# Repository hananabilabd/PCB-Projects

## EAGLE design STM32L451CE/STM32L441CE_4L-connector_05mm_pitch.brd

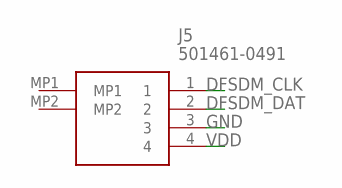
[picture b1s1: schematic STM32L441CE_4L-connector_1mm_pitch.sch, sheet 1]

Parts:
J5: 501461-0491; 5014610491

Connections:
DFSDM_CLK: J5.1; also elsewhere on the board
DFSDM_DAT: J5.2; also elsewhere on the board
GND: J5.3; also elsewhere on the board
VDD: J5.4; also elsewhere on the board

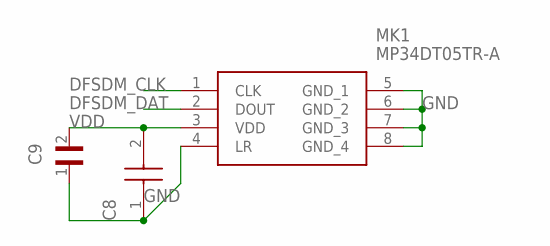
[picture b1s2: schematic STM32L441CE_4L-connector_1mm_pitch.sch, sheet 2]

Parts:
C8: AMK063AC6105KP-F; CAPC0603X33N
C9: GRM033C80J104KE15D; CAPC0603X33N
MK1: MP34DT05TR-A; MP34DT05TRA

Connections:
DFSDM_CLK: MK1.1 (CLK); also elsewhere on the board
DFSDM_DAT: MK1.2 (DOUT); also elsewhere on the board
GND: C8.1, C9.1, MK1.4 (LR), MK1.5 (GND_1), MK1.6 (GND_2), MK1.7 (GND_3), MK1.8 (GND_4); also elsewhere on the board
VDD: C8.2, C9.2, MK1.3 (VDD); also elsewhere on the board

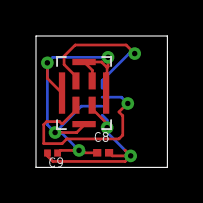
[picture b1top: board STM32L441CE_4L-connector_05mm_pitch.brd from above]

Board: 4 copper layers, 7.3 x 7.3 mm, 4 parts (1 on the bottom side), 4 nets.

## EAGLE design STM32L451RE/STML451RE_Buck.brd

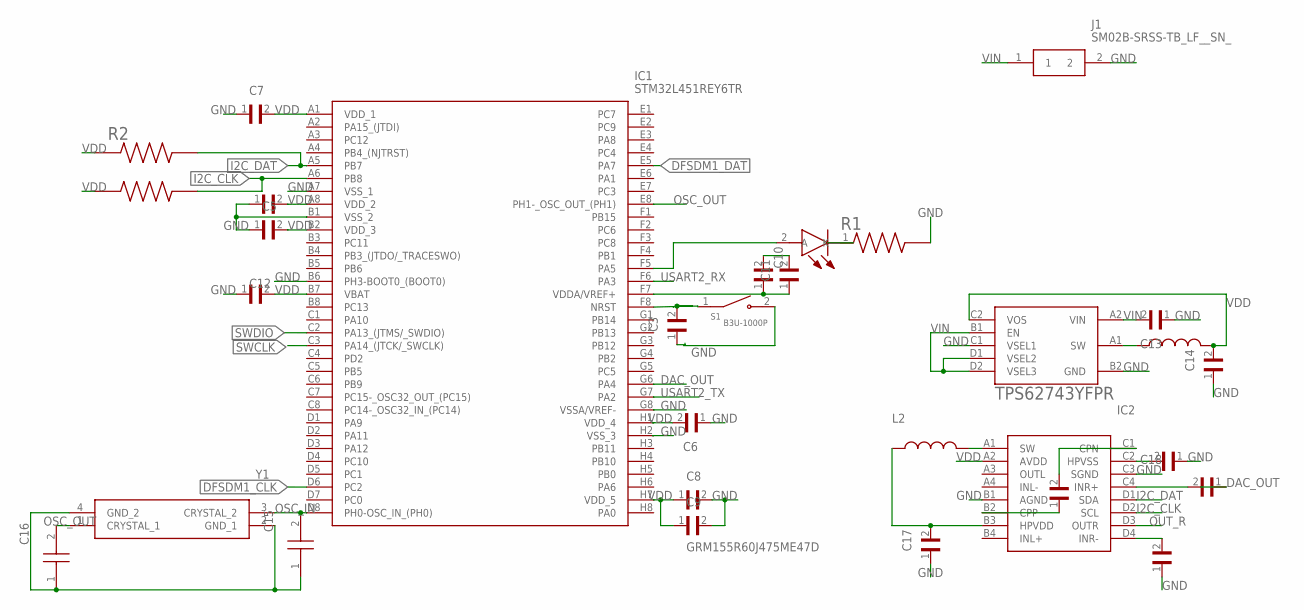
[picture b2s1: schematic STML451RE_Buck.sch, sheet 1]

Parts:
C3, C4, C5, C6, C7, C8, C10, C12: GRM033C80J104KE15D; CAPC0603X33N
C9, C13: GRM155R60J475ME47D; CAPC1005X60N
C11, C19, C20, C21: JMK105C6105KV-F; CAPC1005X55N
C14: GRM155R60J106ME15D; CAPC1005X65N
C15, C16: 0101YA120JAT2A; CAPC0402X22N
C17, C18: GRM155R60J225KE95D; CAPC1005X55N
IC1: STM32L451REY6TR; BGA64C40P8X8_336X366X58
IC2: TPA6140A2YFFT; BGA16C40P4X4_156X156X63
J1: SM02B-SRSS-TB_LF__SN_; SM02B-SRSS-TB
L1: 1285AS-H-2R2M=P2; INDC2016X100N
L2: LQM21PN2R2MC0D; INDC2012X55N
LED1: VLMS1500-GS08; VLMG1500GS08
R1: CRCW02012K20FKED; RESC0603X28N
R2, R3: ERA-2AEB122X; RESC1005X40N
S1: B3U-1000P; SW_B3U-1000P
U1: TPS62743YFPR; BGA8N40P2X4_87X156X50
Y1: FL0800008Q

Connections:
DAC_OUT: C21.1, IC1.G6 (PA4)
DFSDM1_CLK: IC1.D6 (PC2); also elsewhere on the board
DFSDM1_DAT: IC1.E5 (PA7); also elsewhere on the board
GND: C3.1, C4.1, C5.1, C6.1, C7.1, C8.2, C9.2, C12.1, C13.1, C14.1, C15.1, C16.1, C17.1, C18.1, C20.1, IC1.A7 (VSS_1), IC1.B1 (VSS_2), IC1.B6 (PH3-BOOT0_(BOOT0)), IC1.G8 (VSSA/VREF-), IC1.H2 (VSS_3), IC2.B1 (AGND), IC2.C3 (SGND), J1.2, R1.2, U1.B2 (GND), U1.C1 (VSEL1), Y1.2 (GND_1), Y1.4 (GND_2); also elsewhere on the board
I2C_CLK: IC1.A6 (PB8), IC2.D2 (SCL), R3.2
I2C_DAT: IC1.A5 (PB7), IC2.D1 (SDA), R2.2
unnamed: IC1.F5 (PA5), LED1.2 (A)
unnamed: C3.2, S1.1
unnamed: C10.1, C11.1, IC1.F7 (VDDA/VREF+)
unnamed: C10.2, C11.2
unnamed: LED1.1 (K), R1.1
unnamed: C17.2, IC2.B3 (HPVDD), L2.1
unnamed: L1.1, U1.A1 (SW)
unnamed: IC2.A1 (SW), L2.2
unnamed: C18.2, IC2.C2 (HPVSS)
unnamed: C19.1, IC2.B2 (CPP)
unnamed: C19.2, IC2.C1 (CPN)
unnamed: C21.2, IC2.C4 (INR+)
unnamed: C20.2, IC2.D4 (INR-)
OSC_IN: C15.2, IC1.D8 (PH0-OSC_IN_(PH0)), Y1.3 (CRYSTAL_2)
OSC_OUT: C16.2, IC1.E8 (PH1-_OSC_OUT_(PH1)), Y1.1 (CRYSTAL_1)
OUT_R: IC2.D3 (OUTR)
SWCLK: IC1.C3 (PA14_(JTCK/_SWCLK))
SWDIO: IC1.C2 (PA13_(JTMS/_SWDIO))
USART2_RX: IC1.F6 (PA3)
USART2_TX: IC1.G7 (PA2)
VDD: C4.2, C5.2, C6.2, C7.2, C8.1, C9.1, C12.2, C14.2, IC1.A1 (VDD_1), IC1.A8 (VDD_2), IC1.B2 (VDD_3), IC1.B7 (VBAT), IC1.H1 (VDD_4), IC1.H7 (VDD_5), IC2.A2 (AVDD), L1.2, R2.1, R3.1, U1.C2 (VOS); also elsewhere on the board
VIN: C13.2, J1.1, U1.A2 (VIN), U1.B1 (EN), U1.D1 (VSEL2), U1.D2 (VSEL3)

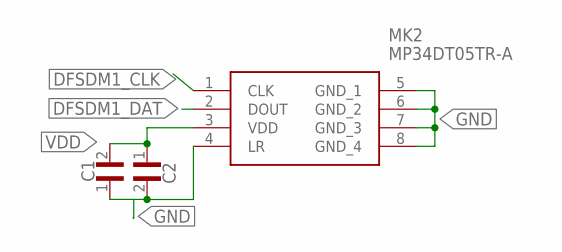
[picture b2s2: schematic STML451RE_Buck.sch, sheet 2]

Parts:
C1: GRM033C80J104KE15D; CAPC0603X33N
C2: JMK105C6105KV-F; CAPC1005X55N
MK2: MP34DT05TR-A; MP34DT05TRA

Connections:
DFSDM1_CLK: MK2.1 (CLK); also elsewhere on the board
DFSDM1_DAT: MK2.2 (DOUT); also elsewhere on the board
GND: MK2.5 (GND_1), MK2.6 (GND_2), MK2.7 (GND_3), MK2.8 (GND_4); also elsewhere on the board
unnamed: C1.1, C2.2, MK2.4 (LR)
VDD: C1.2, C2.1, MK2.3 (VDD); also elsewhere on the board

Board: 2 copper layers, 34 parts (0 on the bottom side), 24 nets, no tracks yet.

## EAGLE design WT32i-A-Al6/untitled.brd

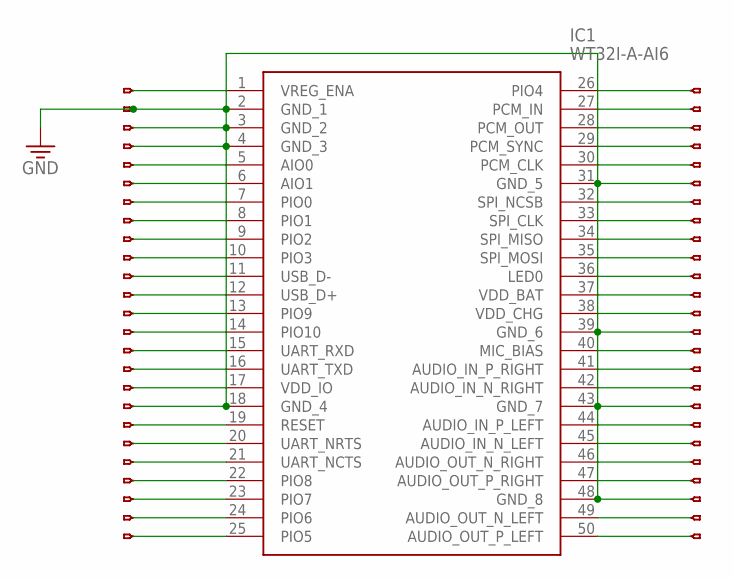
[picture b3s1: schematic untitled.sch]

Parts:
IC1: WT32I-A-AI6
JP1, JP2, JP3, JP4, JP5, JP6, JP7, JP8, JP9, JP10, JP11, JP12, JP13, JP14, JP15, JP16, JP17, JP18, JP19, JP20, JP21, JP22, JP23, JP24, JP25, JP26, JP27, JP28, JP29, JP30, JP31, JP32, JP33, JP34, JP35, JP36, JP37, JP38, JP39, JP40, JP41, JP42, JP43, JP44, JP45, JP46, JP47, JP48, JP49, JP50: HEADERHOLE-HEADERHOLE; 1X1-HEADER-HOLE

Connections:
GND: IC1.2 (GND_1), IC1.3 (GND_2), IC1.4 (GND_3), IC1.18 (GND_4), IC1.31 (GND_5), IC1.39 (GND_6), IC1.43 (GND_7), IC1.48 (GND_8), JP2.1, JP3.1, JP4.1, JP18.1, JP31.1, JP39.1, JP43.1, JP48.1
unnamed: IC1.1 (VREG_ENA), JP1.1
unnamed: IC1.5 (AIO0), JP5.1
unnamed: IC1.6 (AIO1), JP6.1
unnamed: IC1.7 (PIO0), JP7.1
unnamed: IC1.8 (PIO1), JP8.1
unnamed: IC1.9 (PIO2), JP9.1
unnamed: IC1.10 (PIO3), JP10.1
unnamed: IC1.11 (USB_D-), JP11.1
unnamed: IC1.12 (USB_D+), JP12.1
unnamed: IC1.13 (PIO9), JP13.1
unnamed: IC1.14 (PIO10), JP14.1
unnamed: IC1.15 (UART_RXD), JP15.1
unnamed: IC1.16 (UART_TXD), JP16.1
unnamed: IC1.17 (VDD_IO), JP17.1
unnamed: IC1.19 (RESET), JP19.1
unnamed: IC1.20 (UART_NRTS), JP20.1
unnamed: IC1.21 (UART_NCTS), JP21.1
unnamed: IC1.22 (PIO8), JP22.1
unnamed: IC1.23 (PIO7), JP23.1
unnamed: IC1.24 (PIO6), JP24.1
unnamed: IC1.25 (PIO5), JP25.1
unnamed: IC1.26 (PIO4), JP26.1
unnamed: IC1.27 (PCM_IN), JP27.1
unnamed: IC1.28 (PCM_OUT), JP28.1
unnamed: IC1.29 (PCM_SYNC), JP29.1
unnamed: IC1.30 (PCM_CLK), JP30.1
unnamed: IC1.32 (SPI_NCSB), JP32.1
unnamed: IC1.33 (SPI_CLK), JP33.1
unnamed: IC1.34 (SPI_MISO), JP34.1
unnamed: IC1.35 (SPI_MOSI), JP35.1
unnamed: IC1.36 (LED0), JP36.1
unnamed: IC1.37 (VDD_BAT), JP37.1
unnamed: IC1.38 (VDD_CHG), JP38.1
unnamed: IC1.40 (MIC_BIAS), JP40.1
unnamed: IC1.41 (AUDIO_IN_P_RIGHT), JP41.1
unnamed: IC1.42 (AUDIO_IN_N_RIGHT), JP42.1
unnamed: IC1.44 (AUDIO_IN_P_LEFT), JP44.1
unnamed: IC1.45 (AUDIO_IN_N_LEFT), JP45.1
unnamed: IC1.46 (AUDIO_OUT_N_RIGHT), JP46.1
unnamed: IC1.47 (AUDIO_OUT_P_RIGHT), JP47.1
unnamed: IC1.49 (AUDIO_OUT_N_LEFT), JP49.1
unnamed: IC1.50 (AUDIO_OUT_P_LEFT), JP50.1

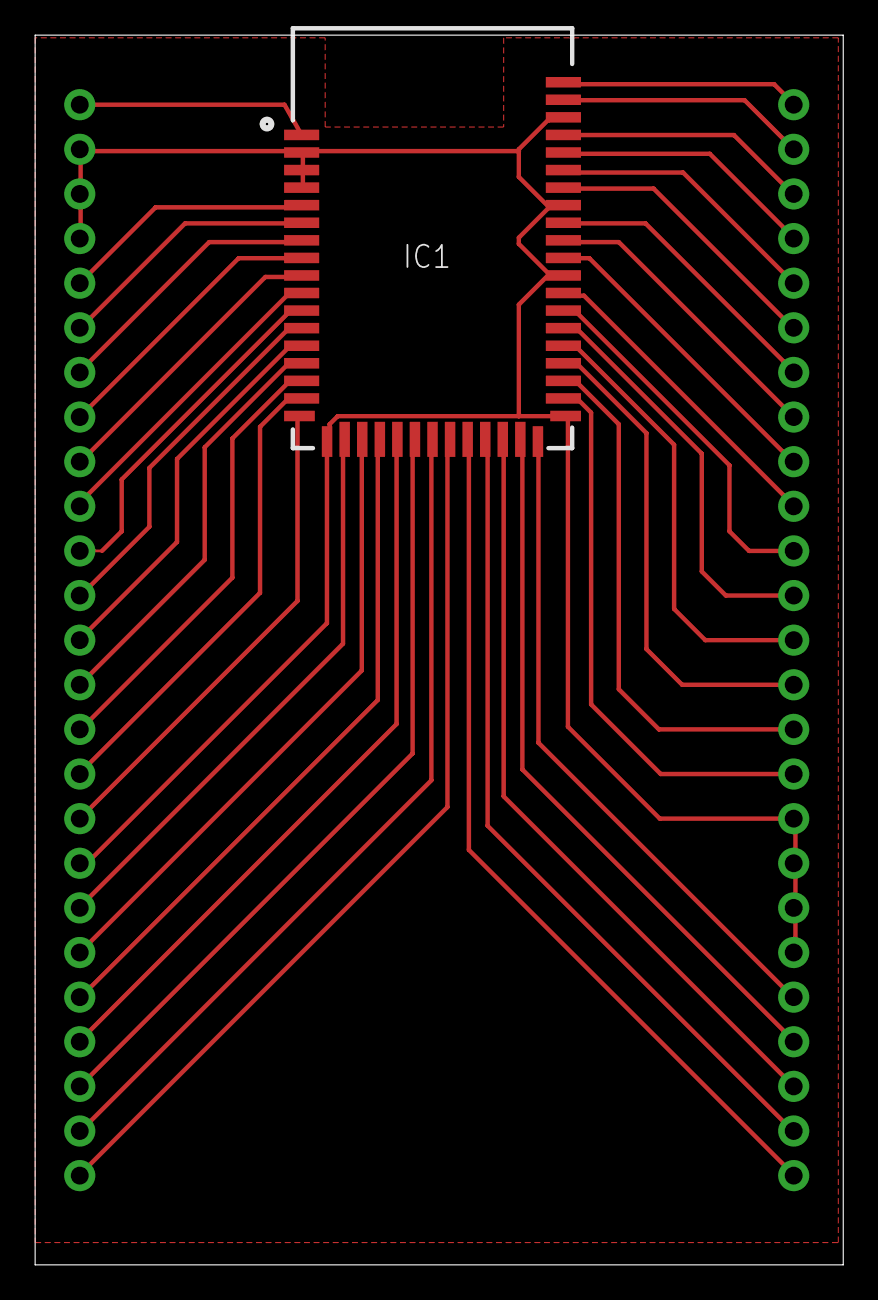
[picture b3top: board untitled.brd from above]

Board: 2 copper layers, 46.0 x 70.0 mm, 51 parts (0 on the bottom side), 43 nets.

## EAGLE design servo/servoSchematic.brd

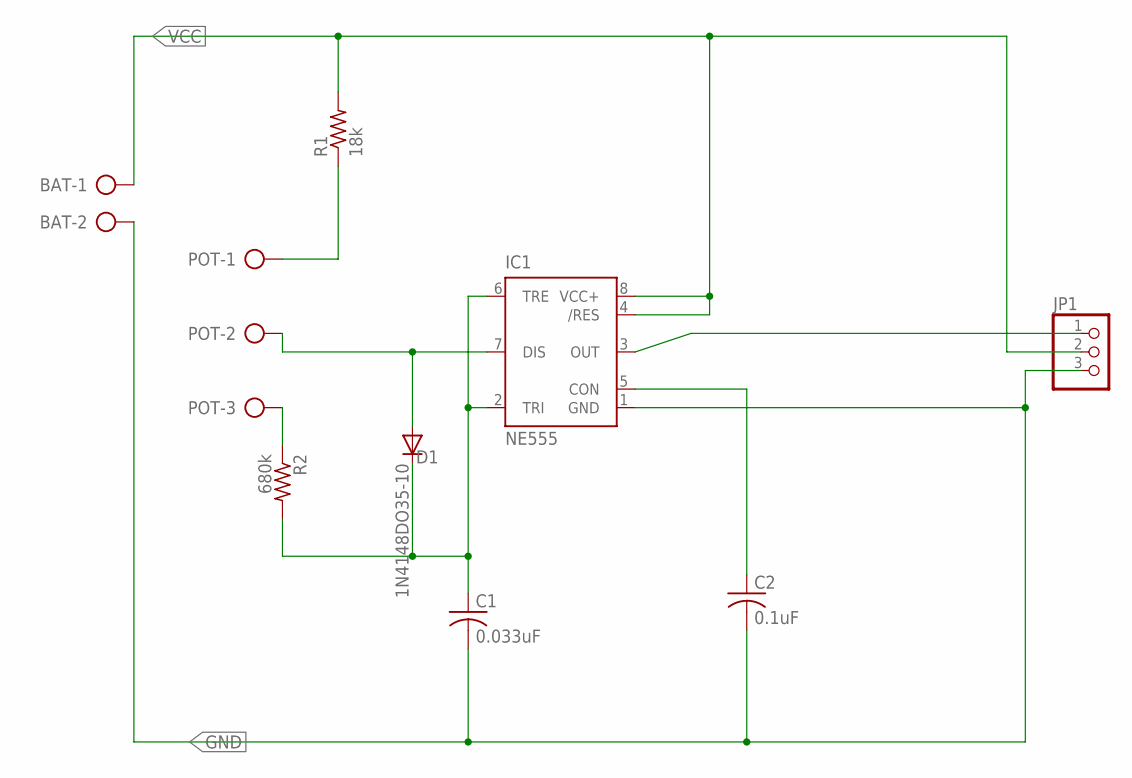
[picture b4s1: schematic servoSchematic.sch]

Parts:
BAT: AK500/2
C1: 0.033uF; C025-024X044
C2: 0.1uF; C025-024X044
D1: 1N4148DO35-10; DO35-10
IC1: NE555; DIL-08
JP1: PINHD-1X3/90; 1X03/90
POT: AK500/3
R1: 18k; 0204/7
R2: 680k; 0204/7

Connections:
GND: BAT.2, C1.2, C2.2, IC1.1 (GND), JP1.3
unnamed: POT.1, R1.1
unnamed: C1.1, D1.C, IC1.2 (TRI), IC1.6 (TRE), R2.2
unnamed: D1.A, IC1.7 (DIS), POT.2
unnamed: POT.3, R2.1
unnamed: IC1.3 (OUT), JP1.1
unnamed: C2.1, IC1.5 (CON)
VCC: BAT.1, IC1.4 (/RES), IC1.8 (VCC+), JP1.2, R1.2

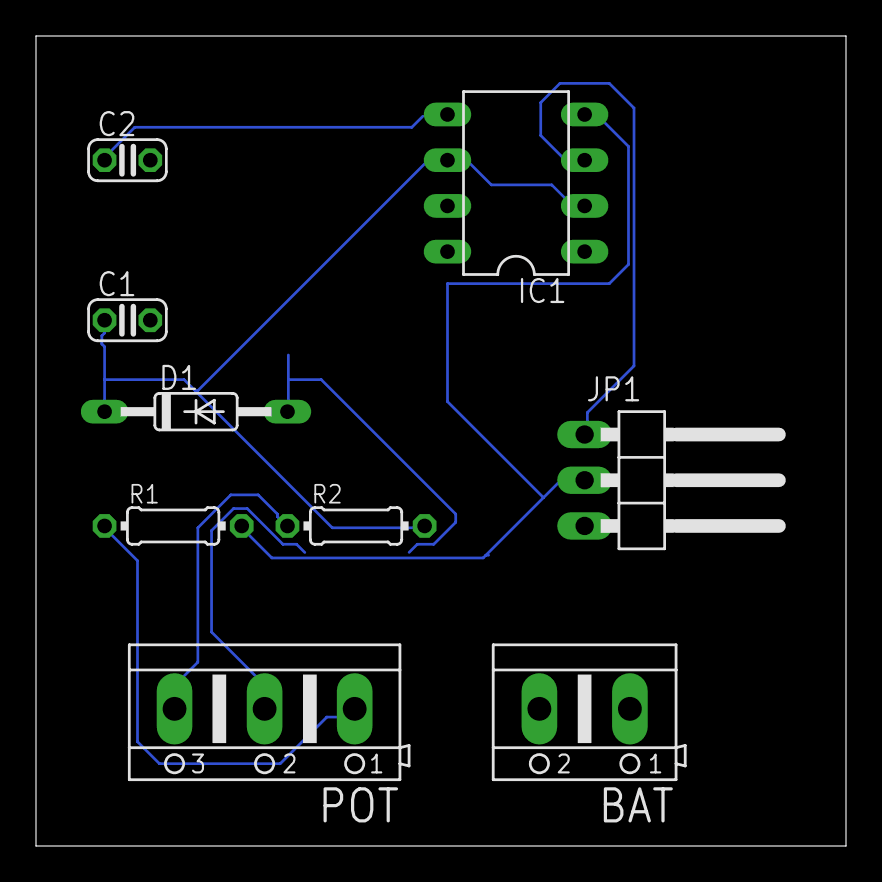
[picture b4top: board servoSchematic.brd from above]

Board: 2 copper layers, 45.0 x 45.0 mm, 9 parts (0 on the bottom side), 8 nets.
